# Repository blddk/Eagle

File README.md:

Eagle
=====
This is where I am going to put new, and move other Eagle projects, into.

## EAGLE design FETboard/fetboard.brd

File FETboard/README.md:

Partlist

Exported from fetboard.brd at 18-08-2014 21:45:08

EAGLE Version 7.0.0 Copyright (c) 1988-2014 CadSoft

Assembly variant: 

Part     Value          Package      Library  Position (inch)       Orientation

AUX-2    M05X2PTH       AVR_ICSP     SparkFun (0.4 1.5)             R90
D44                     1X02         pinhead  (0.15 0.2)            R270
D59                     1X02         pinhead  (0.15 0.6)            R270
D64                     1X02         pinhead  (0.65 0.6)            R270
D66                     1X02         pinhead  (0.65 0.2)            R270
FET1     IPG20N04S4L-11 SUPERSO8     4pi      (0.4 0.7)             R180
FET2     IPG20N04S4L-11 SUPERSO8     4pi      (0.4 0.28)            R180
IN                      1X02         pinhead  (0.15 1.05)           R270
L44                     CHIPLED_0805 adafruit (0.15 0.35)           R270
L59                     CHIPLED_0805 adafruit (0.15 0.75)           R270
L64                     CHIPLED_0805 adafruit (0.65 0.75)           R90
L66                     CHIPLED_0805 adafruit (0.65 0.35)           R90
R1       5k             0805         SparkFun (0.325 1.03)          R90
R2       5k             0805         SparkFun (0.425 1.03)          R90
R3       5k             0805         SparkFun (0.525 1.03)          R90
R4       5k             0805         SparkFun (0.625 1.03)          R90
R5       33r            0805         SparkFun (0.425 1.25)          R270
R6       33r            0805         SparkFun (0.325 1.25)          R270
R7       33r            0805         SparkFun (0.525 1.25)          R270
R8       33r            0805         SparkFun (0.625 1.25)          R270
R9       1k             0805         SparkFun (0.65 0.42)           R0
R10      1k             0805         SparkFun (0.15 0.42)           R180
R11      1k             0805         SparkFun (0.65 0.82)           R0
R12      1k             0805         SparkFun (0.15 0.82)           R180

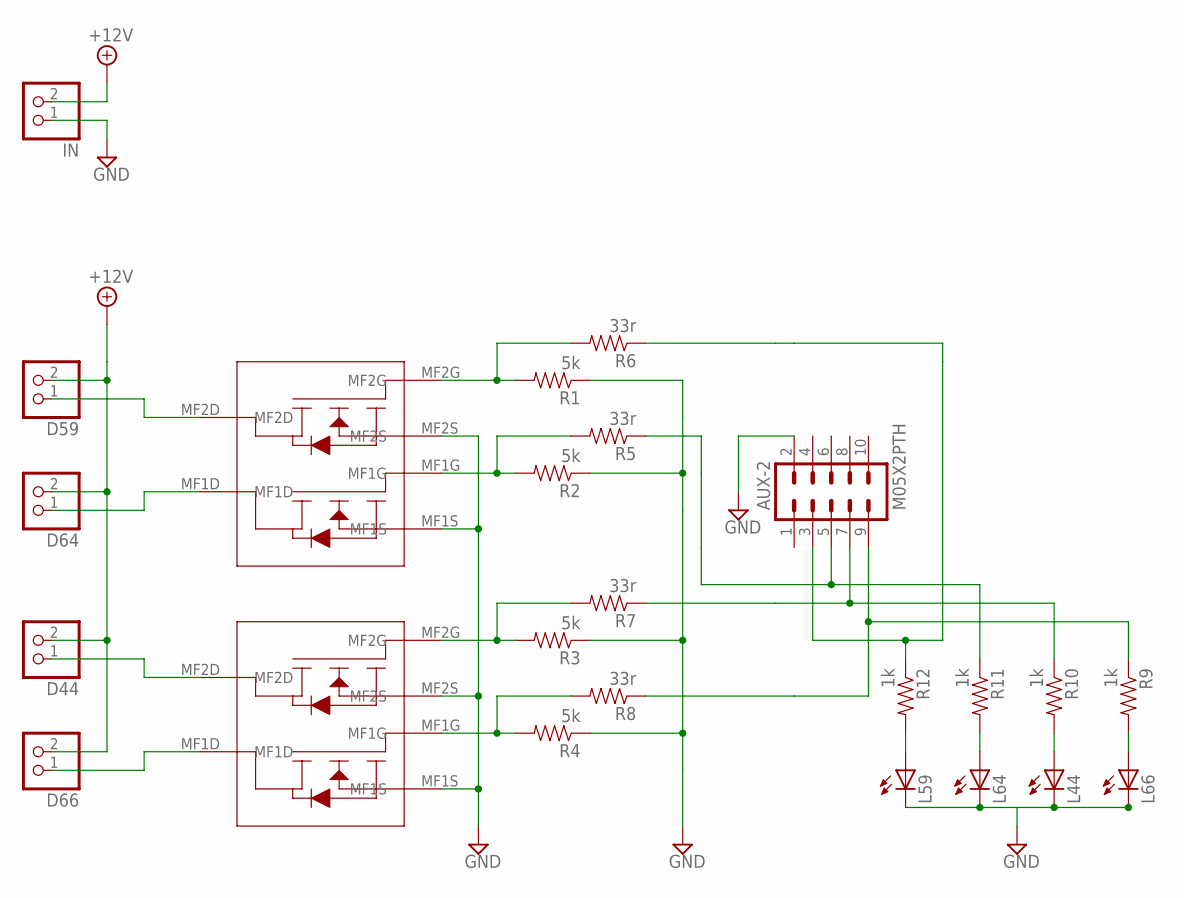
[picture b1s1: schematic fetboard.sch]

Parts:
AUX-2: M05X2PTH; AVR_ICSP
D44, D59, D64, D66: PINHD-1X2; 1X02
FET1, FET2: IPG20N04S4L-11; SUPERSO8
IN: PINHD-1X2; 1X02
L44, L59, L64, L66: LEDCHIPLED_0805; CHIPLED_0805
R1, R2, R3, R4: 5k; 0805
R5, R6, R7, R8: 33r; 0805
R9, R10, R11, R12: 1k; 0805

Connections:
+12V: D44.2, D59.2, D64.2, D66.2, IN.2
GND: AUX-2.2, FET1.MF1S, FET1.MF2S, FET2.MF1S, FET2.MF2S, IN.1, L44.C, L59.C, L64.C, L66.C, R1.1, R2.1, R3.1, R4.1
unnamed: AUX-2.3, R6.1, R12.1
unnamed: FET1.MF1G, R2.2, R5.2
unnamed: L59.A, R12.2
unnamed: FET2.MF1G, R4.2, R8.2
unnamed: FET2.MF2G, R3.2, R7.2
unnamed: FET1.MF2G, R1.2, R6.2
unnamed: AUX-2.7, R7.1, R10.1
unnamed: AUX-2.9, R8.1, R9.1
unnamed: AUX-2.5, R5.1, R11.1
unnamed: L64.A, R11.2
unnamed: L44.A, R10.2
unnamed: L66.A, R9.2
unnamed: D64.1, FET1.MF1D
unnamed: D44.1, FET2.MF2D
unnamed: D66.1, FET2.MF1D
unnamed: D59.1, FET1.MF2D

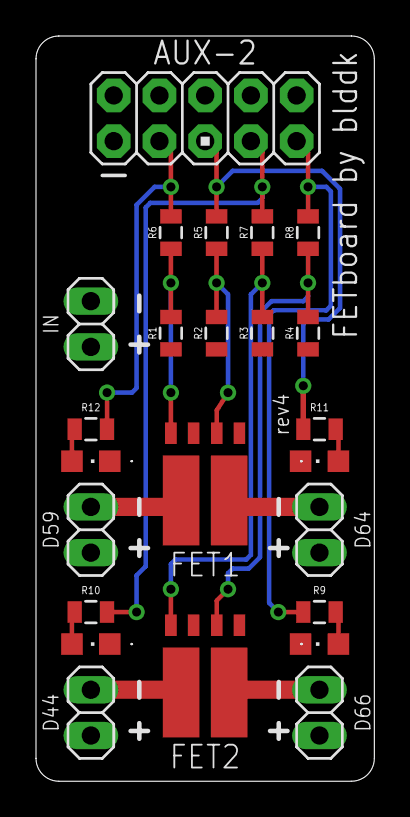
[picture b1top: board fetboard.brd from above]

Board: 2 copper layers, 18.8 x 41.4 mm, 25 parts (0 on the bottom side), 18 nets.

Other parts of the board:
U$3: OSHWLOGO_TOL_0.2

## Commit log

2014-08-18 :lollipop: Added .gitattributes & .gitignore files
2014-08-18 FETboard
    Adding 4 extra mosfet outputs by using AUX-2 on RAMPS
2014-08-18 Added readme

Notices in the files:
parts and their libraries:
SparkFun: Licensing: CC v3.0 Share-Alike You are welcome to use this library for commercial purposes.
